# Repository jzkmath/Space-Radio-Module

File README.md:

# Space-Radio-Module
Design for radio module that can be used in cubesats.

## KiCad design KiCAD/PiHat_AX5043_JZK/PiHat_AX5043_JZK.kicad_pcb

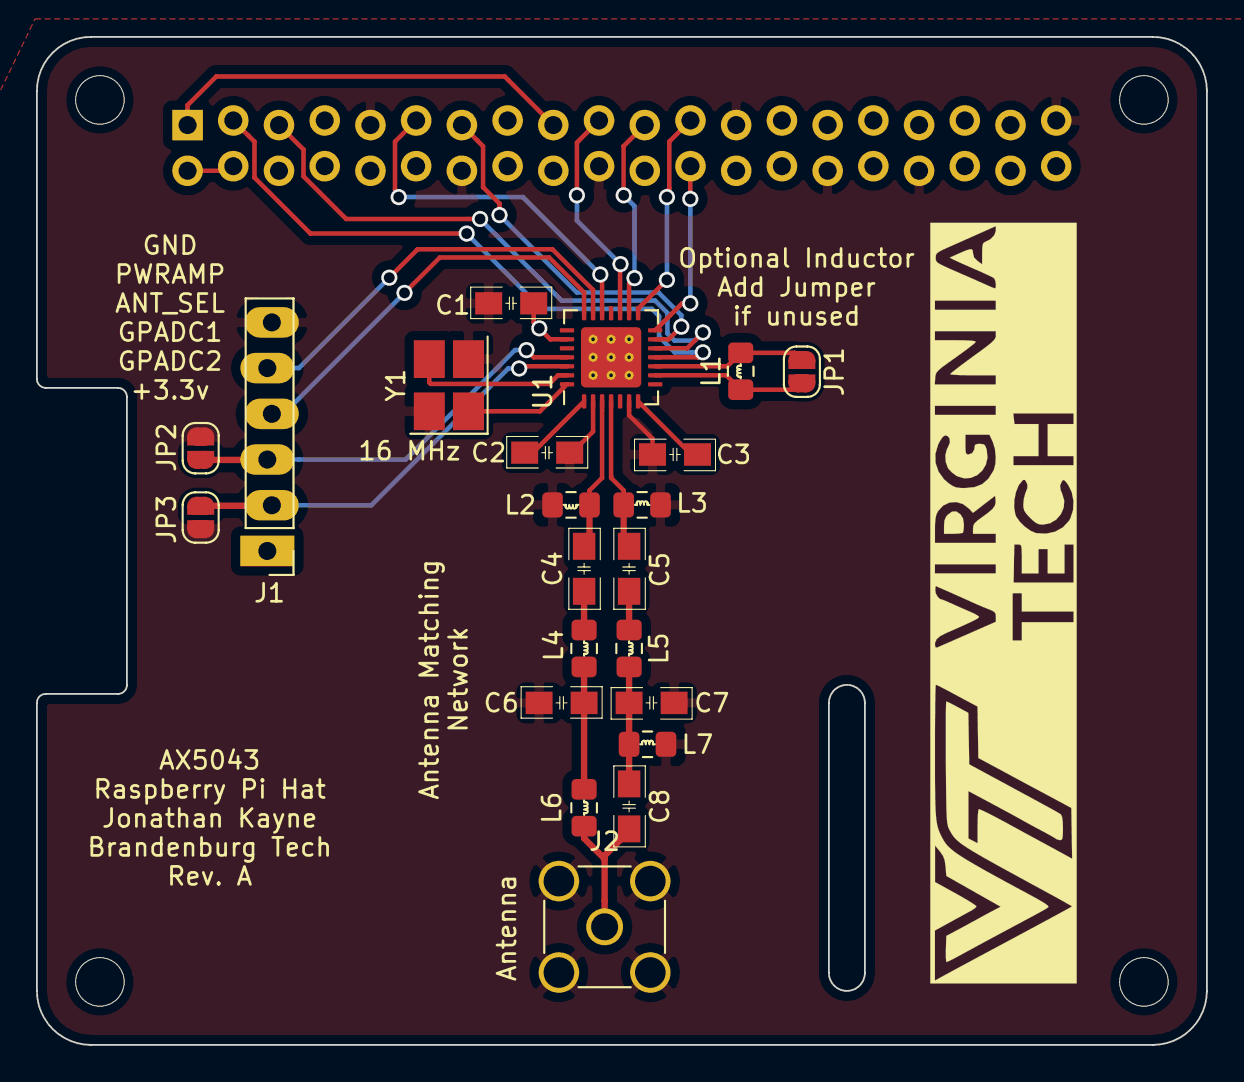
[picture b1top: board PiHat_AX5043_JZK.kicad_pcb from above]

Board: 4 copper layers, 65.0 x 56.0 mm, 27 parts (1 on the bottom side), 28 nets.

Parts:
C1, C2, C3: 10nF; C_0805
C4, C5: 4.3pF; C_0805
C6: 11pF; C_0805
C7: 5.6pF; C_0805
C8: 5.1pF; C_0805
J1: Conn_01x06; PinHeader_1x06_P2.54mm_Vertical_Wide_zigzag
J2: SMA; SMA_Amphenol_5-1814832-1_Vertical
JP1, JP2, JP3: Jumper; SolderJumper-2_P1.3mm_Open_RoundedPad1.0x1.5mm
L1: L; L_0805
L2, L3: 100nH; L_0805
L4, L5: 43nH; L_0805
L6, L7: 27nH; L_0805
MK1, MK2, MK3, MK4: M2.5; MountingHole_2.7mm_M2.5
P1: Conn_02x20_Odd_Even; PinHeader_2x20_P2.54mm_Vertical_zigzag
U1: AX5043; QFN-28-1EP_5x5mm_P0.5mm_EP3.35x3.35mm_ThermalVias
Y1: 16 MHz; Crystal_SMD_SeikoEpson_TSX3225-4Pin_3.2x2.5mm_HandSoldering

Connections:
+3V3: C1.1, J1.1, P1.1, P1.17, U1.23
+5V: P1.2, P1.4
ANT_N: C5.2, L3.1, U1.4
ANT_P: C4.2, L2.1, U1.3
ANT_SEL: J1.4, U1.21
CLK: P1.23, U1.15
CS: P1.24, U1.14
Data_CLK: P1.5, U1.12
Data_IO: P1.3, U1.11
GND: C1.2, C2.1, C3.1, C6.2, C7.2, J1.6, J2.2, JP2.2, JP3.2, L2.2, L3.2, L7.2, P1.6, P1.9, P1.14, P1.20, P1.25, P1.30, P1.34, P1.39, U1.2, U1.6, U1.29, Y1.2, Y1.4
GPADC1: J1.3, JP2.1, U1.25
GPADC2: J1.2, JP3.1, U1.26
IRQ: P1.11, U1.19
MISO: P1.21, U1.16
MOSI: P1.19, U1.17
unnamed: C2.2, U1.1
unnamed: C3.2, U1.7
unnamed: C4.1, L4.1
unnamed: C5.1, L5.1
unnamed: C6.1, L4.2, L6.1
unnamed: C7.1, C8.2, L5.2, L7.1
unnamed: C8.1, J2.1, L6.2
unnamed: JP1.1, L1.2, U1.10
unnamed: JP1.2, L1.1, U1.9
unnamed: U1.27, Y1.3
unnamed: U1.28, Y1.1
PWRAMP: J1.5, U1.20
SYS_CLK: P1.13, U1.13

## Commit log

2019-06-07 Pi Hat test
2019-06-24 Linked Footprints
